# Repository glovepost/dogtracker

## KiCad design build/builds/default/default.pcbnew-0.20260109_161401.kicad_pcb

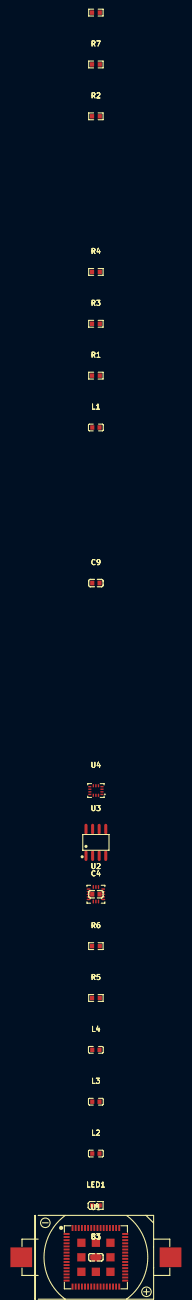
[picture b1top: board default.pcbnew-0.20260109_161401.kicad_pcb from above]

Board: 2 copper layers, 21 parts (0 on the bottom side), 12 nets, no tracks yet.

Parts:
B1: BAT-TH_CR2032-BS-6-1
C3, C4, C9: 100nF ±10% 50V X7R; C0603
L1, L2, L3, L4: 10µH ±20% 30MHz 50mA 1.17Ω; L0603
LED1: LED0603-RD
R1, R2, R3, R4, R5, R6, R7, R8: 10kΩ ±1% 100mW; R0603
U1: LGA-73_L12.0-W12.0-P0.60-TL
U2: LGA-16_L3.0-W3.0-P0.50-TL
U3: SOIC-8_L4.9-W3.9-P1.27-LS6.0-BL
U4: LGA-14_L3.0-W2.5-P0.50-BR

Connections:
A: LED1.2, R6.2
INT1: U1.15, U2.11
activation: R5.2, U1.42
adc_ntc: R3.1, R4.2, U1.45
footprint-INT2-0: U1.58, U4.9
footprint-INT2-1: U1.14, U2.9
gnd: B1.2, C3.2, C4.2, C9.2, LED1.1, R1.2, R3.2, U1.12, U1.28, U1.35, U1.36, U1.38, U1.39, U1.46, U1.47, U1.52, U1.56, U1.65, U1.66, U1.67, U1.68, U1.69, U1.70, U1.71, U1.72, U1.73, U2.5, U2.12, U3.4, U3.7, U4.4, U4.6, U4.7
i2c_scl: R8.2, U1.8, U2.4, U3.6, U4.13
i2c_sda: R7.2, U1.17, U2.6, U3.5, U4.14
led_status: R6.1, U1.16
vbat: B1.1, L2.1, U1.4
vcc: C3.1, C4.1, C9.1, L1.1, L1.2, L2.2, L3.1, L3.2, L4.1, L4.2, R1.1, R4.1, R5.1, R7.1, R8.1, U1.3, U1.7, U1.53, U1.54, U1.55, U2.1, U2.14, U3.8, U4.5, U4.8

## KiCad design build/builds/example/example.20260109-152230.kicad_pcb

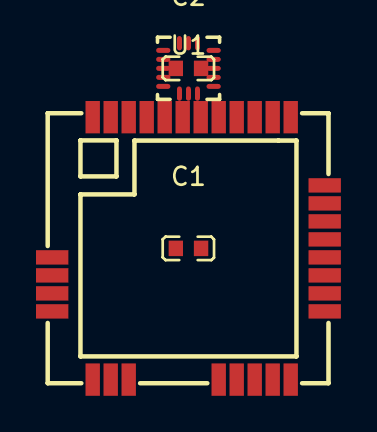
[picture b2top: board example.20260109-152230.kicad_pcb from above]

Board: 2 copper layers, 4 parts (0 on the bottom side), 4 nets, no tracks yet.

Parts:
C1, C2: L0603
U1: LCC-40_L15.6-W15.0-P1.00_RAK3172
U2: LGA-16_L3.0-W3.0-P0.50-TL

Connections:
gnd: C1.2, C2.2, U1.11, U1.17, U1.18, U1.23, U1.28, U2.5, U2.12
i2c_scl: U1.3, U2.4
i2c_sda: U1.4, U2.6
vcc: C1.1, C2.1, U1.24, U2.1, U2.14

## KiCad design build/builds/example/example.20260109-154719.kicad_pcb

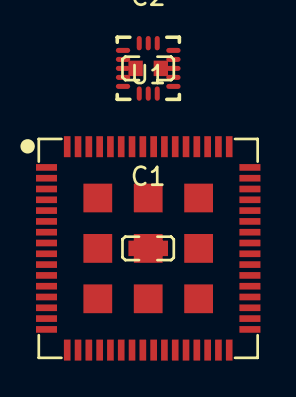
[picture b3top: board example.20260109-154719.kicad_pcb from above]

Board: 2 copper layers, 4 parts (0 on the bottom side), 4 nets, no tracks yet.

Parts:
C1, C2: L0603
U1: LGA-73_L12.0-W12.0-P0.60-TL
U2: LGA-16_L3.0-W3.0-P0.50-TL

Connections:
gnd: C1.2, C2.2, U1.12, U1.28, U1.35, U1.36, U1.38, U1.39, U1.46, U1.47, U1.52, U1.56, U1.65, U1.66, U1.67, U1.68, U1.69, U1.70, U1.71, U1.72, U1.73, U2.5, U2.12
i2c_scl: U1.8, U2.4
i2c_sda: U1.17, U2.6
vcc: C1.1, C2.1, U1.3, U1.7, U1.53, U1.54, U1.55, U2.1, U2.14

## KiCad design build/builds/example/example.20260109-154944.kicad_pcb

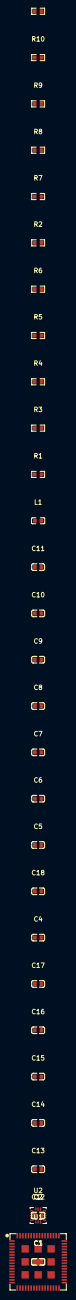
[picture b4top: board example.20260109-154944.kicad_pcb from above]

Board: 2 copper layers, 32 parts (0 on the bottom side), 4 nets, no tracks yet.

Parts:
C1, C2: L0603
C3, C4, C5, C6, C7, C8, C9, C10, C11, C12, C13, C14, C15, C16, C17, C18: 100nF ±10% 50V X7R; C0603
L1: 10µH ±20% 30MHz 50mA 1.17Ω; L0603
R1, R2, R3, R4, R5, R6, R7, R8, R9, R10, R11: 10kΩ ±1% 100mW; R0603
U1: LGA-73_L12.0-W12.0-P0.60-TL
U2: LGA-16_L3.0-W3.0-P0.50-TL

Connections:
gnd: C1.2, C2.2, C3.2, C4.2, C5.2, C6.2, C7.2, C8.2, C9.2, C10.2, C11.2, C12.2, C13.2, C14.2, C15.2, C16.2, C17.2, C18.2, U1.12, U1.28, U1.35, U1.36, U1.38, U1.39, U1.46, U1.47, U1.52, U1.56, U1.65, U1.66, U1.67, U1.68, U1.69, U1.70, U1.71, U1.72, U1.73, U2.5, U2.12
i2c_scl: R8.2, U1.8, U2.4
i2c_sda: R7.2, U1.17, U2.6
vcc: C1.1, C2.1, C3.1, C4.1, C5.1, C6.1, C7.1, C8.1, C9.1, C10.1, C11.1, C12.1, C13.1, C14.1, C15.1, C16.1, C17.1, C18.1, R7.1, R8.1, U1.3, U1.7, U1.53, U1.54, U1.55, U2.1, U2.14
